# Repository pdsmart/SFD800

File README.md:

# SFD800
A Floppy Disk Interface card for the Sharp MZ series of machines (MZ-80B/MZ-800/MZ-1500/MZ-2000/MZ-2200).

This project reproduces an iconic floppy disk interface card from the 1980's. As floppy disks were expensive in those days, not many interface cards or floppy 
disk drives existed and even fewer survived. As the Sharp MZ series machines, like many of the old computers, are still used and in many ways making a comeback,
the need for a floppy disk interface is needed in order to use the machines.

Please see my website, https://eaw.app for more documentation and any recent updates. This interface has been well tested and used in many machines, a validated design.

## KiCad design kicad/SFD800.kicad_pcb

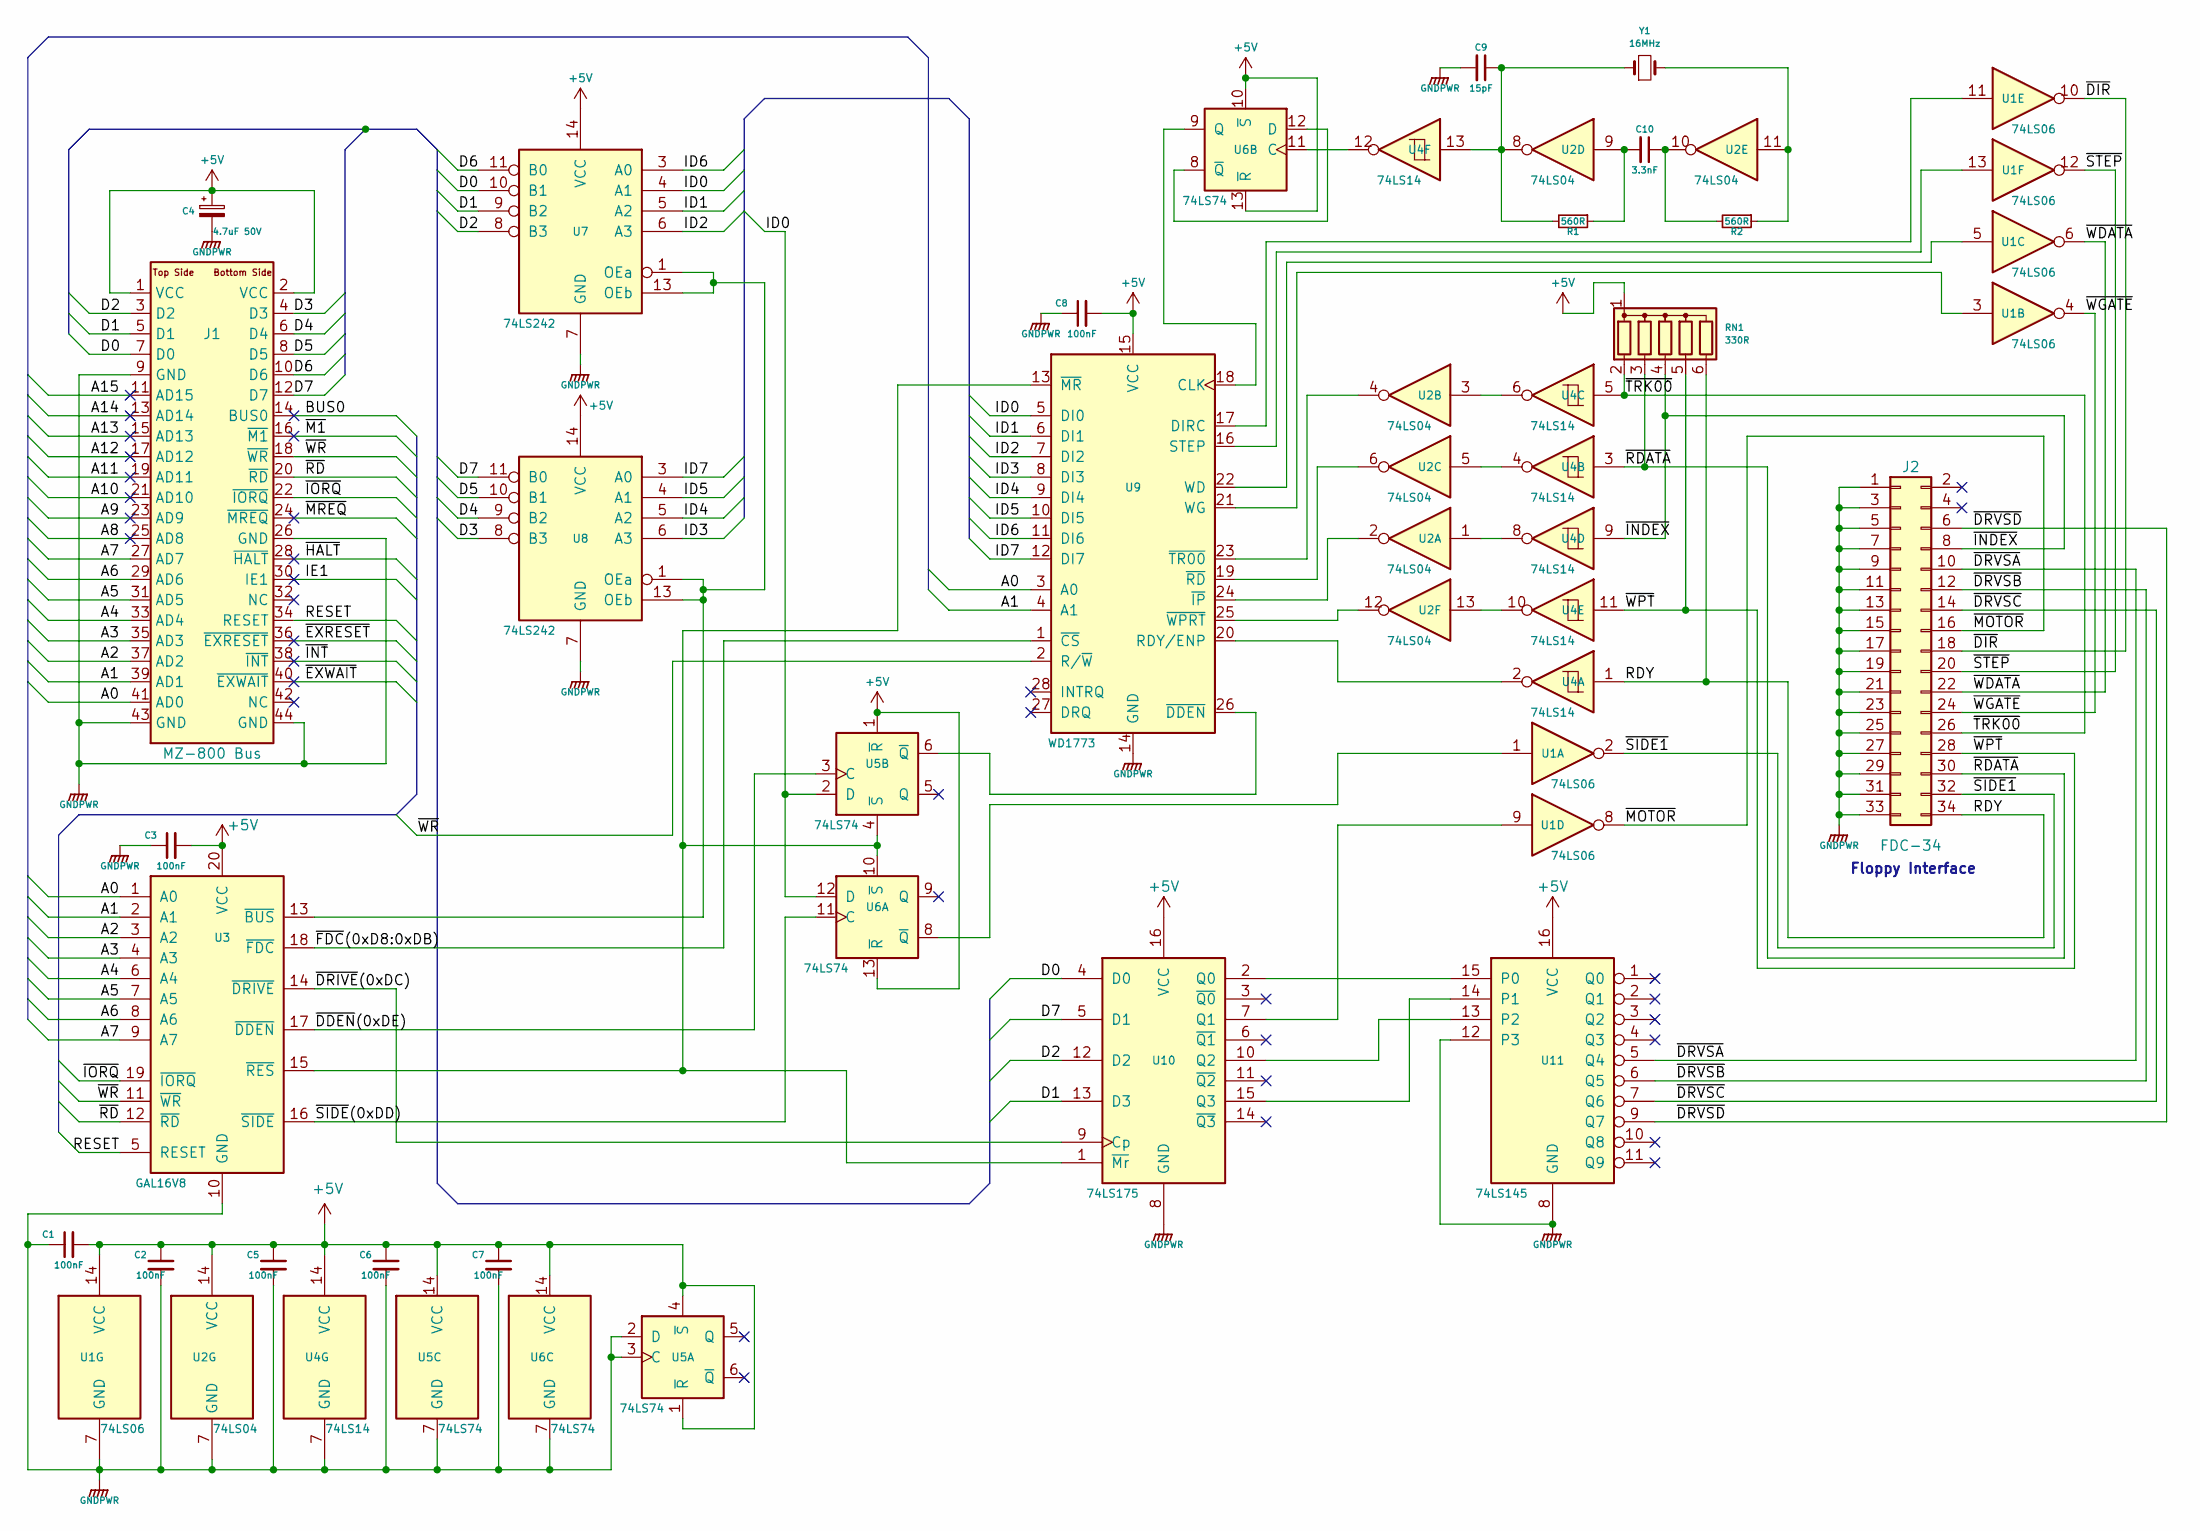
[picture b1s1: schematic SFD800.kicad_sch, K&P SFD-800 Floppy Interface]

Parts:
C1, C2, C3, C5, C6, C7, C8: 100nF; C_Disc_D5.0mm_W2.5mm_P2.50mm
C4: 4.7uF 50V; C_Disc_D5.0mm_W2.5mm_P2.50mm
C9: 15pF; C_Disc_D5.0mm_W2.5mm_P2.50mm
C10: 3.3nF; C_Disc_D5.0mm_W2.5mm_P2.50mm
J1: MZ-800 Bus; BUS_MZ800
J2: FDC-34; IDC-Header_2x17_P2.54mm_Horizontal_Lock_SFD800
R1, R2: 560R; R_Axial_DIN0204_L3.6mm_D1.6mm_P5.08mm_Horizontal
RN1: 330R; R_Array_SIP6
U1: 74LS06; DIP-14_W7.62mm
U2: 74LS04; DIP-14_W7.62mm
U3: GAL16V8; DIP-20_W7.62mm
U4: 74LS14; DIP-14_W7.62mm
U5, U6: 74LS74; DIP-14_W7.62mm
U7, U8: 74LS242; DIP-14_W7.62mm
U9: WD1773; DIP-28_W15.24mm
U10: 74LS175; DIP-16_W7.62mm
U11: 74LS145; DIP-16_W7.62mm
Y1: 16MHz; Crystal_HC18-U_Horizontal

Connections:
+5V: C1.2, C2.1, C3.2, C4.1, C5.1, C6.1, C7.1, C8.2, J1.1 (VCC), J1.2 (VCC), RN1.1 (common), U1.14 (VCC), U2.14 (VCC), U3.20 (VCC), U4.14 (VCC), U5.1 (~R), U5.4 (~S), U5.13 (~R), U5.14 (VCC), U6.1 (~R), U6.10 (~S), U6.13 (~R), U6.14 (VCC), U7.14 (VCC), U8.14 (VCC), U9.15 (VCC), U10.16 (VCC), U11.16 (VCC)
/A0: J1.41 (AD0), U3.1 (A0), U9.3 (A0)
/A1: J1.39 (AD1), U3.2 (A1), U9.4 (A1)
/A2: J1.37 (AD2), U3.3 (A2)
/A3: J1.35 (AD3), U3.4 (A3)
/A4: J1.33 (AD4), U3.6 (A4)
/A5: J1.31 (AD5), U3.7 (A5)
/A6: J1.29 (AD6), U3.8 (A6)
/A7: J1.27 (AD7), U3.9 (A7)
/A8: J1.25 (AD8)
/A9: J1.23 (AD9)
/A10: J1.21 (AD10)
/A11: J1.19 (AD11)
/A12: J1.17 (AD12)
/A13: J1.15 (AD13)
/A14: J1.13 (AD14)
/A15: J1.11 (AD15)
/BUS0: J1.14 (BUS0)
/D0: J1.7 (D0), U7.10 (B1), U10.4 (D0)
/D1: J1.5 (D1), U7.9 (B2), U10.13 (D3)
/D2: J1.3 (D2), U7.8 (B3), U10.12 (D2)
/D3: J1.4 (D3), U8.8 (B3)
/D4: J1.6 (D4), U8.9 (B2)
/D5: J1.8 (D5), U8.10 (B1)
/D6: J1.10 (D6), U7.11 (B0)
/D7: J1.12 (D7), U8.11 (B0), U10.5 (D1)
/ID0: U5.12 (D), U6.2 (D), U7.4 (A1), U9.5 (DI0)
/ID1: U7.5 (A2), U9.6 (DI1)
/ID2: U7.6 (A3), U9.7 (DI2)
/ID3: U8.6 (A3), U9.8 (DI3)
/ID4: U8.5 (A2), U9.9 (DI4)
/ID5: U8.4 (A1), U9.10 (DI5)
/ID6: U7.3 (A0), U9.11 (DI6)
/ID7: U8.3 (A0), U9.12 (DI7)
/IE1: J1.30 (IE1)
/RESET: J1.34 (RESET), U3.5 (RESET)
/~EXRESET: J1.36 (~EXRESET)
/~EXWAIT: J1.40 (~EXWAIT)
/~HALT: J1.28 (~HALT)
/~INT: J1.38 (~INT)
/~IORQ: J1.22 (~IORQ), U3.19 (~IORQ)
/~M1: J1.16 (~M1)
/~MREQ: J1.24 (~MREQ)
/~RD: J1.20 (~RD), U3.12 (~RD)
/~WR: J1.18 (~WR), U3.11 (~WR), U9.2 (R/~W)
GNDPWR: C1.1, C2.2, C3.1, C4.2, C5.2, C6.2, C7.2, C8.1, C9.2, J1.9 (GND), J1.26 (GND), J1.43 (GND), J1.44 (GND), J2.1, J2.3, J2.5, J2.7, J2.9, J2.11, J2.13, J2.15, J2.17, J2.19, J2.21, J2.23, J2.25, J2.27, J2.29, J2.31, J2.33, U1.7 (GND), U2.7 (GND), U3.10 (GND), U4.7 (GND), U5.2 (D), U5.3 (C), U5.7 (GND), U6.7 (GND), U7.7 (GND), U8.7 (GND), U9.14 (GND), U10.8 (GND), U11.8 (GND), U11.12 (P3)
unnamed: C9.1, R1.2, U2.8, U4.13, Y1.1
unnamed: C10.1, R2.2, U2.10
unnamed: C10.2, R1.1, U2.9
unnamed: J2.6, U11.9 (Q7)
unnamed: J2.8, RN1.4 (R3), U4.9
unnamed: J2.10, U11.5 (Q4)
unnamed: J2.12, U11.6 (Q5)
unnamed: J2.14, U11.7 (Q6)
unnamed: J2.16, U1.8
unnamed: J2.18, U1.10
unnamed: J2.20, U1.12
unnamed: J2.22, U1.6
unnamed: J2.24, U1.4
unnamed: J2.26, RN1.2 (R1), U4.5
unnamed: J2.28, RN1.5 (R4), U4.11
unnamed: J2.30, RN1.3 (R2), U4.3
unnamed: J2.32, U1.2
unnamed: J2.34, RN1.6 (R5), U4.1
unnamed: R2.1, U2.11, Y1.2
unnamed: U1.1, U5.8 (~Q)
unnamed: U1.3, U9.21 (WG)
unnamed: U1.5, U9.22 (WD)
unnamed: U1.9, U10.7 (Q1)
unnamed: U1.11, U9.17 (DIRC)
unnamed: U1.13, U9.16 (STEP)
unnamed: U2.1, U4.8
unnamed: U2.2, U9.24 (~IP)
unnamed: U2.3, U4.6
unnamed: U2.4, U9.23 (~TR00)
unnamed: U2.5, U4.4
unnamed: U2.6, U9.19 (~RD)
unnamed: U2.12, U9.25 (~WPRT)
unnamed: U2.13, U4.10
unnamed: U3.13 (~BUS), U7.1 (OEa), U7.13 (OEb), U8.1 (OEa), U8.13 (OEb)
unnamed: U3.16 (~SIDE), U5.11 (C)
unnamed: U3.17 (~DDEN), U6.3 (C)
unnamed: U3.18 (~FDC), U9.1 (~CS)
unnamed: U4.2, U9.20 (RDY/ENP)
unnamed: U4.12, U6.11 (C)
unnamed: U6.6 (~Q), U9.26 (~DDEN)
unnamed: U6.9 (Q), U9.18 (CLK)
unnamed: U6.8 (~Q), U6.12 (D)
unnamed: U3.15 (~RES), U5.10 (~S), U6.4 (~S), U9.13 (~MR), U10.1 (~Mr)
unnamed: U10.2 (Q0), U11.15 (P0)
unnamed: U3.14 (~DRIVE), U10.9 (Cp)
unnamed: U10.10 (Q2), U11.13 (P2)
unnamed: U10.15 (Q3), U11.14 (P1)

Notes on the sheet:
Floppy Interface

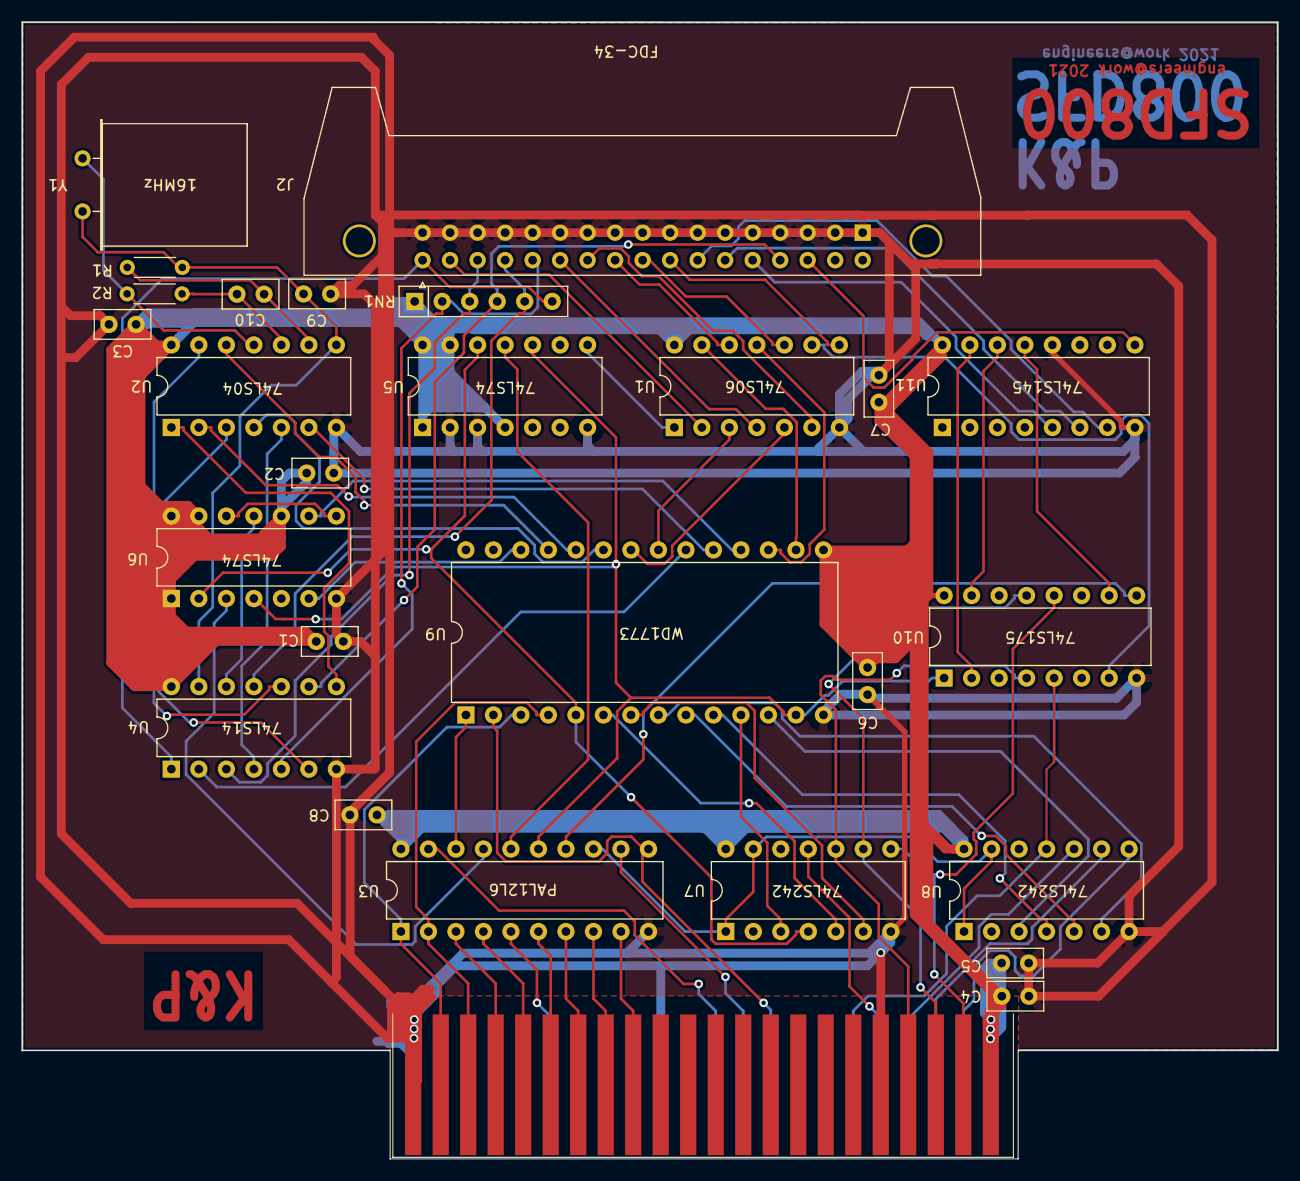
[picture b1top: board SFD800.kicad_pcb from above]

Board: 2 copper layers, 116.0 x 105.0 mm, 27 parts (0 on the bottom side), 77 nets.

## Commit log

2022-03-11 First push
2022-03-11 Added README
2023-05-10 Updates to add CUPL and dosbox config files for CUPL compilation
